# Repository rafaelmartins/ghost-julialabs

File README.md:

# ghost-julialabs

PCI para o desafio de halloween 2022 do canal [julialabs na Twitch](https://www.twitch.tv/julialabs).

Layout baseado na skin básica de fantasma do jogo Among Us.

## Hardware

### Placa de Circuito Impresso

#### Produção

Arquivo `.zip` com Gerbers disponivel [aqui](/pcb/gerber/). Para produzir as placas basta fazer upload do zip no site da [PCBWay](https://www.pcbway.com/) ou similar.

### Esquemático

### Lista de Materiais

ID     | Description                   | Mouser No.
------ | ----------------------------- | ------------------------------------------------------------------------------
U1     | Microcontrolador ATtiny85-20S | [556-ATTINY85-20SF](https://www.mouser.de/ProductDetail/556-ATTINY85-20SF)
D1     | LED SMD Verde "Side View"     | [710-155060VS75300](https://www.mouser.de/ProductDetail/710-155060VS75300)
D2     | LED SMD Vermelho "Side View"  | [710-155060SS75300](https://www.mouser.de/ProductDetail/710-155060SS75300)
R1, R2 | Resistor SMD 47R 0603         | [603-RC0603FR-0747RL](https://www.mouser.de/ProductDetail/603-RC0603FR-0747RL)
C1     | Capacitor SMD 100nF 0603      | [810-C0603X7S1A104K](https://www.mouser.de/ProductDetail/810-C0603X7S1A104K)
BT1    | Suporte para bateria CR2032   | [534-1058](https://www.mouser.de/ProductDetail/534-1058)
SW1    | Chave SPDT ON-ON              | [611-PCM12SMTR](https://www.mouser.de/ProductDetail/611-PCM12SMTR)

## Software

Acesse o [release mais recente](https://github.com/rafaelmartins/ghost-julialabs/releases/latest) e faça o download do arquivo `ghost-julialabs.hex`. Grave o conteúdo deste arquivo na memória flash do `ATtiny85` da forma que achar mais conveniente. A forma mais popular entre os makers consiste na utilização do [AVRDUDE](https://www.nongnu.org/avrdude/) com um gravador de baixo custo como o [USBasp](https://www.fischl.de/usbasp/). A utilização dos mesmos foge do escopo desse documento.

A seguinte configuração de `fuses` do `ATtiny85` é necessaria para o correto funcionamento (podem ser gravados utilizando a mesma ferramenta que gravou o firmware na memória flash):

```
low=0xE2, high=0x9F, extended=0xFF, lockbit=0xFF
```

## License

Original work is released under the BSD 3-Clause (firmware) and CERN Open Hardware Licence Version 2 - Strongly Reciprocal (pcb).

This project is based on Among Us game artwork, and should be covered by the [Innersloth Fan Creation Policy](https://www.innersloth.com/fan-creation-policy/). Based on drawing from [xcolorings.com (via Pinterest)](https://www.pinterest.com/pin/584834701606097283/).

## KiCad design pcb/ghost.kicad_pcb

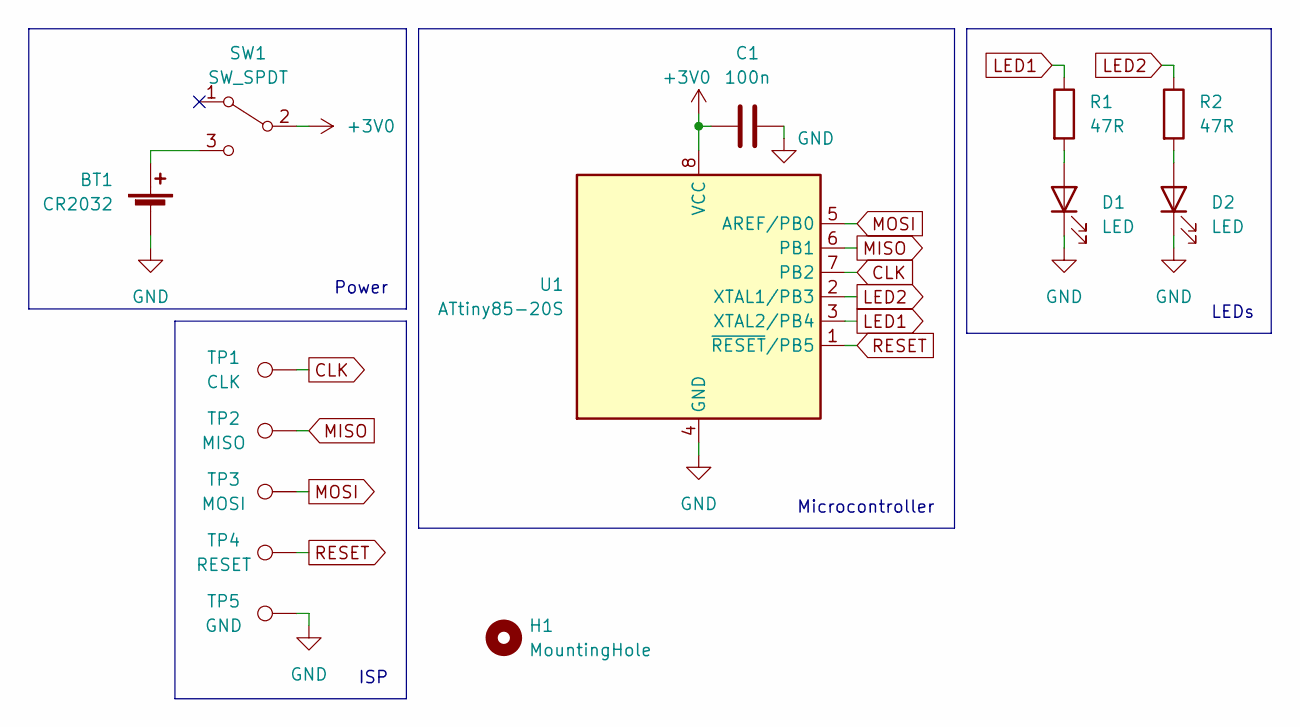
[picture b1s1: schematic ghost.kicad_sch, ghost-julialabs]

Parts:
BT1: CR2032; BatteryHolder_Keystone_1058_1x2032
C1: 100n; C_0603_1608Metric
D1, D2: LED; LED_0805_2012Metric
H1: MountingHole; MountingHole_2.2mm_M2
R1, R2: 47R; R_0603_1608Metric
SW1: SW_SPDT; SW_SPDT_PCM12
TP1: CLK; TestPoint_Pad_1.0x1.0mm
TP2: MISO; TestPoint_Pad_1.0x1.0mm
TP3: MOSI; TestPoint_Pad_1.0x1.0mm
TP4: RESET; TestPoint_Pad_1.0x1.0mm
TP5: GND; TestPoint_Pad_1.0x1.0mm
U1: ATtiny85-20S; SOIC-8W_5.3x5.3mm_P1.27mm

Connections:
+3V0: C1.1, SW1.2 (B), U1.8 (VCC)
CLK: TP1.1, U1.7 (PB2)
GND: BT1.2 (-), C1.2, D1.1 (K), D2.1 (K), TP5.1, U1.4 (GND)
LED1: R1.1, U1.3 (XTAL2/PB4)
LED2: R2.1, U1.2 (XTAL1/PB3)
MISO: TP2.1, U1.6 (PB1)
MOSI: TP3.1, U1.5 (AREF/PB0)
unnamed: BT1.1 (+), SW1.3 (C)
unnamed: D1.2 (A), R1.2
unnamed: D2.2 (A), R2.2
RESET: TP4.1, U1.1 (~RESET/PB5)

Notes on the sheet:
ISP
Power
LEDs
Microcontroller

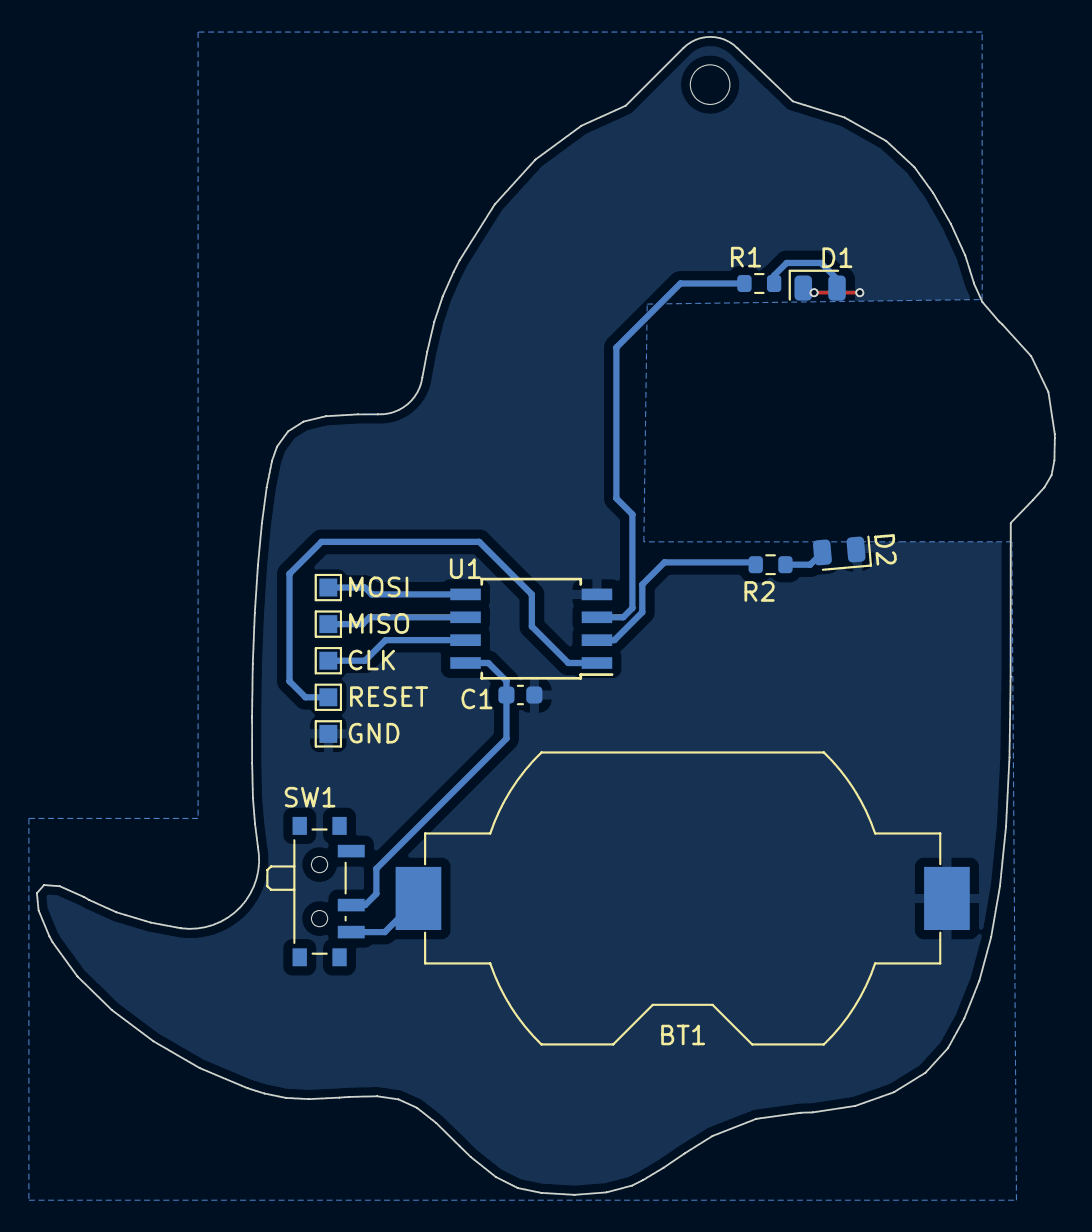
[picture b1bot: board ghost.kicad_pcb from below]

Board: 2 copper layers, 56.6 x 64.3 mm, 14 parts (13 on the bottom side), 11 nets.

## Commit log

2022-08-25 Commit inicial.
2022-09-06 adiciona firmware
2022-09-19 altera resistores dos leds
2022-09-19 atualiza imagem do esquematico
2022-09-25 Atualiza leds utilizados na montagem final
2022-09-25 adiciona fotos
2022-09-25 compila codigo automaticamente usando github actions
2022-09-25 actions: corrige pasta do firmware
2022-09-25 firmware: desabilita geracao de hex para fuses
2022-09-25 atualiza readme com informacoes sobre a utilizacao do software
2022-09-30 pcb: corrige gerber
